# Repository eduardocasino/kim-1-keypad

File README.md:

# KIM-1 Keypad

## About

Welcome to the KIM-1 Keypad repository.

I designed this board for [my KIM-1 PCB replica](https://github.com/eduardocasino/kim-1), but it will also work with real KIM-1s from Revision D and onwards.

~~WARNING: I have not yet sent the board to fabrication, so it is untested!~~

## Licensing

This is a personal project that I am sharing in case it is of interest to any retrocomputing enthusiast and all the information in this repository is provided "as is", without warranty of any kind. I am not liable for any damages that may occur, whether it be to individuals, objects, KIM-1 computers, kittens or any other pets. It should also be noted that this design has not been tested and may contain errors, therefore anyone who chooses to use it does so at their own risk.

This work is licensed under a [Creative Commons Attribution-NonCommercial 4.0 International License](http://creativecommons.org/licenses/by-nc/4.0/).

EXCEPTION: The electrical schematic and all the associated symbols are licensed under a [Creative Commons Attribution 4.0 International License](https://creativecommons.org/licenses/by/4.0/).

See the LICENSE.md file for details.

## Changelog
#### 05/06/2023
* Fix silkscreen and remove pads from bottom side
## Acknowledgements

* Hans Otten and his [Retro Computing blog](http://retro.hansotten.nl/). Tons of information and high resolution pictures of various KIM-1.
* Ralf (User ralf02 from forum64.de) for info on actual dimensions of the keypad and some high res photos.

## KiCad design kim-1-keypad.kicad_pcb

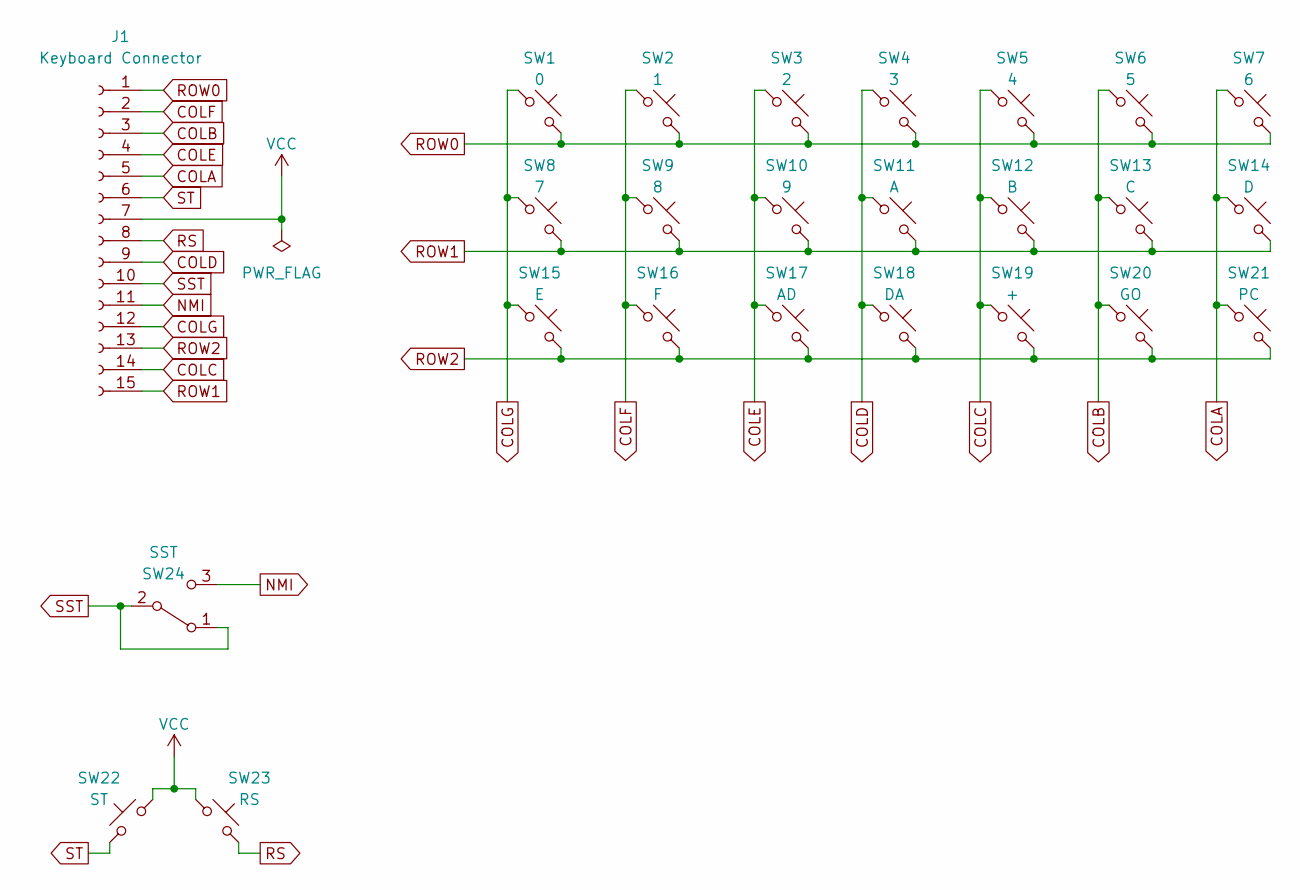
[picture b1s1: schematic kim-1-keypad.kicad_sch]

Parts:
J1: Keyboard Connector; PinHeader_1x15_P2.54mm_Vertical
SW1: 0; SW_SPST_TL3305A
SW2: 1; SW_SPST_TL3305A
SW3: 2; SW_SPST_TL3305A
SW4: 3; SW_SPST_TL3305A
SW5: 4; SW_SPST_TL3305A
SW6: 5; SW_SPST_TL3305A
SW7: 6; SW_SPST_TL3305A
SW8: 7; SW_SPST_TL3305A
SW9: 8; SW_SPST_TL3305A
SW10: 9; SW_SPST_TL3305A
SW11: A; SW_SPST_TL3305A
SW12: B; SW_SPST_TL3305A
SW13: C; SW_SPST_TL3305A
SW14: D; SW_SPST_TL3305A
SW15: E; SW_SPST_TL3305A
SW16: F; SW_SPST_TL3305A
SW17: AD; SW_SPST_TL3305A
SW18: DA; SW_SPST_TL3305A
SW19: +; SW_SPST_TL3305A
SW20: GO; SW_SPST_TL3305A
SW21: PC; SW_SPST_TL3305A
SW22: ST; SW_SPST_TL3305A
SW23: RS; SW_SPST_TL3305A
SW24: SST; JS102011SCQN

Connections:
COLA: J1.5, SW7.1, SW14.1, SW21.1
COLB: J1.3, SW6.1, SW13.1, SW20.1
COLC: J1.14, SW5.1, SW12.1, SW19.1
COLD: J1.9, SW4.1, SW11.1, SW18.1
COLE: J1.4, SW3.1, SW10.1, SW17.1
COLF: J1.2, SW2.1, SW9.1, SW16.1
COLG: J1.12, SW1.1, SW8.1, SW15.1
NMI: J1.11, SW24.3 (C)
ROW0: J1.1, SW1.2, SW2.2, SW3.2, SW4.2, SW5.2, SW6.2, SW7.2
ROW1: J1.15, SW8.2, SW9.2, SW10.2, SW11.2, SW12.2, SW13.2, SW14.2
ROW2: J1.13, SW15.2, SW16.2, SW17.2, SW18.2, SW19.2, SW20.2, SW21.2
RS: J1.8, SW23.1
SST: J1.10, SW24.1 (A), SW24.2 (B)
ST: J1.6, SW22.1
VCC: J1.7, SW22.2, SW23.2

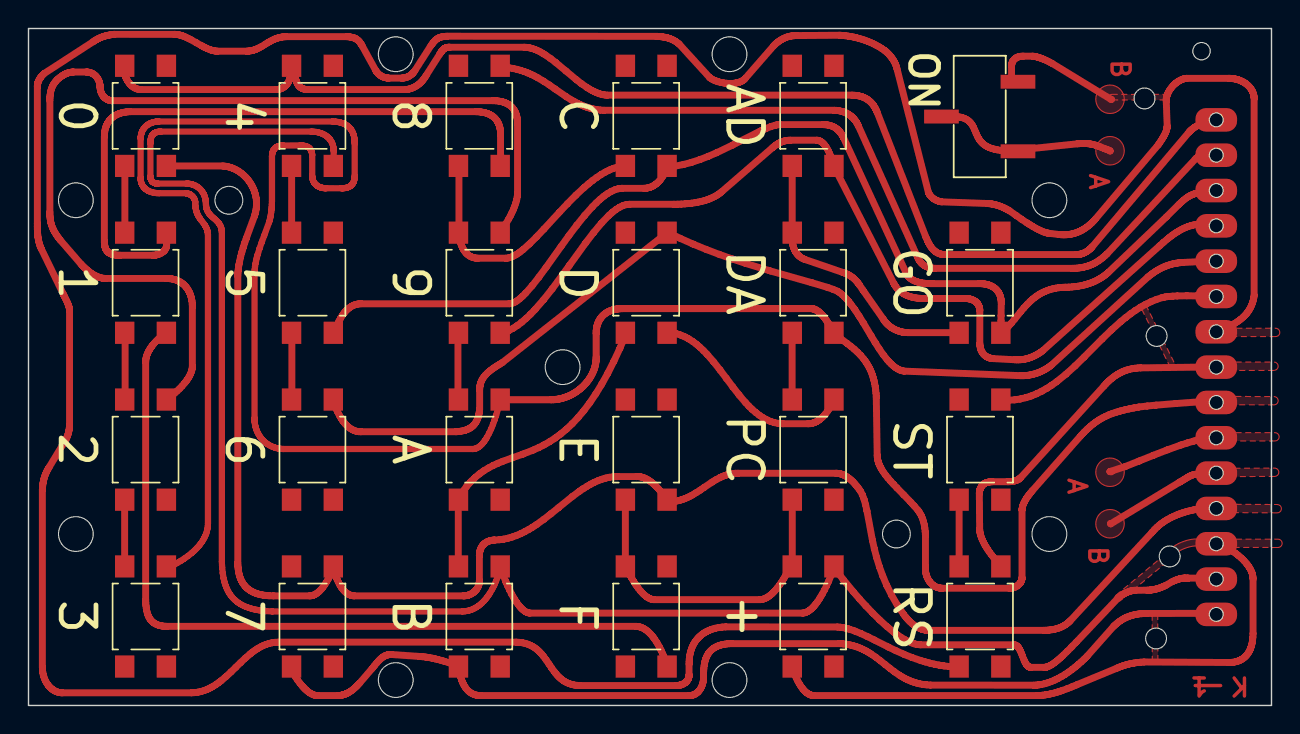
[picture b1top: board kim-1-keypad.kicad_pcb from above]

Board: 2 copper layers, 89.4 x 48.7 mm, 41 parts (0 on the bottom side), 15 nets.

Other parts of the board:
H1, H2, H3, H4, H5, H6, H7, H8, H9#2: MountingHole_2.5mm
H9, H10: MountingHole_2mm
H11, H12, H13, H14: MountingHole_1.5mm
H11#2: MountingHole_1.25mm

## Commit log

2023-05-25 Generate correct gerber files format
2023-06-05 Connector: Remove copper pads from botton side
2023-06-05 Fix silkscreen under slide switch
2023-06-05 Fix silkscreen and connector pads
2023-06-26 Keypad is tested now, remove warning

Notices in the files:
README.md:
Licensing:
[CC BY-NC 4.0](http://creativecommons.org/licenses/by-nc/4.0/)
Th
